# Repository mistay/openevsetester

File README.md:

# Welcome to OpenEVSEtester!

Based on EVSim's documentation (available at https://evsim.gonium.net/) this project tries to automate some basic tests required by [SAE J1772](https://de.wikipedia.org/wiki/SAE_J1772).

By now, this project features a PCB. An upcoming BOM, a Firmware (ESP-IDF) and a mobile app will be relased soon.

# Features
- Wallbox connector 7 PIN: L1, L2, L3, N, PE, CP, PP
- Microcontroller ESP32 (ESP32-S2-WROOM), in-circuit programmable by USB (USB-C) connector or serial (you'll need a $1 programmer, i.e. USB/Serial converter)
- both CP and PP protection by fuses and varistors
- battery (LIpO/LiIo) charger with system load: charge while using this device
- buck/boost converter (3V3) to use any available voltage from battery pack (2,4V to 4,2V)
- UI: display (both i2c oled and/or spi tft) tbd: one of this will be removed in further versions
- UI: rotary encoder for modern menu-browsing
- PE breaker: PE can be disconnected by software to simulate a broken PE wire
- PP isolated proximity resistor selection: choose between 100R, 220R, 680R, 1k5 and 4k7 to or any combination (in parallel) to simulate resistors that are outside specification and to test if the wallbox in test handles the voltage drop according to SAE J1772.
- simulate SAE J1772 states A, B, C and E
- simulate diode-fault by shortening diode
- isolated CP measurment by 10-bit 10ksamples/s adc
- isolated mains (L1, L2, L3) measurement by tranformers and internal ADC of ESP32 (voltage, frequency, phasing)
- cr2032 battery-backuped real time clock to timestamp measurements for reports w/o beeing online

```mermaid
graph LR

A[State A] --> B((read CP: 12V?))

B -- yes --> C[State B]
B -- no --> D(report error)
D --> A
C --> E((CP, PWM?))
E -- no --> G((report error))
G --> A
E -- yes --> F[State C]
F --> H((...))
```

# Firmware

A ESP-IDF based firmware for this device can be found here: https://github.com/mistay/openevsetester_firmware/

# mobile app (html/javascript based web if) (TBD!)
## Requirements
- manual mode (handle and read actuators and sensors)
- trigger automatic testinsg
- report downloading

## Credits
Special thanks for ideas, bugfixes and reviews,  [Philipp Aigner](https://aignerelektronik.at)

## License
MIT

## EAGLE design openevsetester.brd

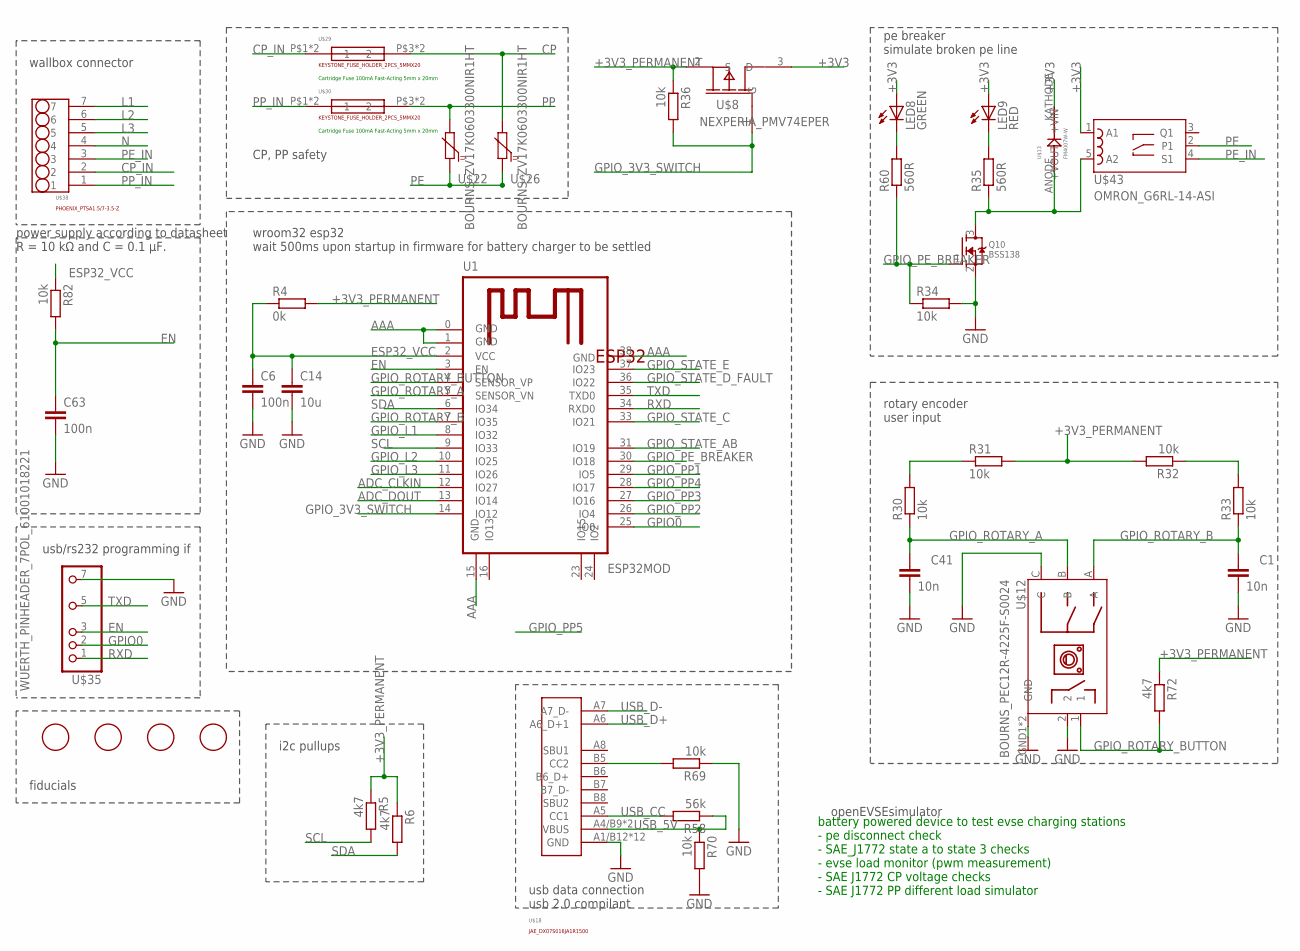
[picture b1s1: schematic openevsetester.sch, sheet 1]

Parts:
C1, C41: 10n; C0402
C6, C63: 100n; C0402
C14: 10u; C0805
LED8: GREEN; SML0603
LED9: RED; SML0603
Q10: BSS138; SOT23
R4: 0k; R0402
R5, R6, R72: 4k7; R0402
R30, R31, R32, R33, R34, R36, R69, R70, R82: 10k; R0402
R35, R60: 560R; R0402
R58: 56k; R0402
U1: ESP32MOD
U$8: NEXPERIA_PMV74EPER; SOT23
U$12: BOURNS_PEC12R-4225F-S0024; BOURNS_PEC12RXXX
U$13: FM4007W-W; SMX
U$18: JAE_DX07S016JA1R1500
U$19, U$21, U$23, U$24: FIDUCIAL; FIDUCIAL_1MM
U$22, U$26: BOURNS_ZV17K0603300NIR1HT; 0603
U$29, U$30: KEYSTONE_FUSE_HOLDER_2PCS_5MMX20; KEYSTONE_PC_5MM_FUSE_CLIP
U$35: WUERTH_PINHEADER_7POL_61001018221; PINHEADER_SMD_7POL_ESP32_PRG
U$38: PHOENIX_PTSA1.5/7-3.5-Z; PHOENIX_PTSA_7POL_3.5MM
U$43: OMRON_G6RL-14-ASI

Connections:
+3V3: LED8.A, LED9.A, U$8.3 (D), U$13.KATHODE (+VOUT), U$43.1 (A1); also elsewhere on the board
+3V3_PERMANENT: R4.2, R5.1, R6.1, R31.2, R32.2, R36.1, R72.1, U$8.2 (S); also elsewhere on the board
AAA: C1.2, C6.2, C14.2, C41.2, C63.2, Q10.2 (S), R34.2, R69.1, R70.2, U1.0 (GND), U1.1 (GND), U1.15 (GND), U1.38 (GND), U$12.2, U$12.C, U$12.GND1 (GND), U$12.GND2 (GND), U$18.A1/B12 (GND), U$18.A12/B1 (GND), U$18.G1 (GND), U$18.G2 (GND), U$18.G3 (GND), U$18.G4 (GND), U$18.G5 (GND), U$18.G6 (GND), U$18.G7 (GND), U$18.G8 (GND), U$18.P1 (GND), U$18.P2 (GND), U$35.7; also elsewhere on the board
ADC_CLKIN: U1.12 (IO27); also elsewhere on the board
ADC_DOUT: U1.13 (IO14); also elsewhere on the board
CP: U$26.1, U$29.P$3 (2), U$29.PAD2 (2); also elsewhere on the board
CP_IN: U$29.P$1 (1), U$29.PAD1 (1), U$38.2
EN: C63.1, R82.2, U1.3 (EN), U$35.3
ESP32_VCC: C6.1, C14.1, R4.1, R82.1, U1.2 (VCC)
GPIO0: U1.25 (IO0), U$35.2
GPIO_3V3_SWITCH: R36.2, U1.14 (IO12), U$8.1 (G)
GPIO_L1: U1.8 (IO32); also elsewhere on the board
GPIO_L2: U1.10 (IO25); also elsewhere on the board
GPIO_L3: U1.11 (IO26); also elsewhere on the board
GPIO_PE_BREAKER: Q10.1 (G), R34.1, R60.1, U1.30 (IO18)
GPIO_PP1: U1.29 (IO5); also elsewhere on the board
GPIO_PP2: U1.26 (IO4); also elsewhere on the board
GPIO_PP3: U1.27 (IO16); also elsewhere on the board
GPIO_PP4: U1.28 (IO17); also elsewhere on the board
GPIO_ROTARY_A: C41.1, R30.1, U1.5 (SENSOR_VN), U$12.B
GPIO_ROTARY_B: C1.1, R33.1, U1.7 (IO35), U$12.A
GPIO_ROTARY_BUTTON: R72.2, U1.4 (SENSOR_VP), U$12.1
GPIO_STATE_AB: U1.31 (IO19); also elsewhere on the board
GPIO_STATE_C: U1.33 (IO21); also elsewhere on the board
GPIO_STATE_D_FAULT: U1.36 (IO22); also elsewhere on the board
GPIO_STATE_E: U1.37 (IO23); also elsewhere on the board
L1: U$38.7; also elsewhere on the board
L2: U$38.6; also elsewhere on the board
L3: U$38.5; also elsewhere on the board
N: U$38.4; also elsewhere on the board
unnamed: LED9.C, R35.2
unnamed: Q10.3 (D), R35.1, U$13.ANODE (+VIN), U$43.5 (A2)
unnamed: LED8.C, R60.2
unnamed: R69.2, U$18.B5 (CC2)
unnamed: R30.2, R31.1
unnamed: R32.1, R33.2
PE: U$22.2, U$26.2, U$43.2 (P1); also elsewhere on the board
PE_IN: U$38.3, U$43.4 (S1)
PP: U$22.1, U$30.P$3 (2), U$30.PAD2 (2); also elsewhere on the board
PP_IN: U$30.P$1 (1), U$30.PAD1 (1), U$38.1
RXD: U1.34 (RXD0), U$35.1
SCL: R5.2, U1.9 (IO33); also elsewhere on the board
SDA: R6.2, U1.6 (IO34); also elsewhere on the board
TXD: U1.35 (TXD0), U$35.5
USB_5V: R58.1, R70.1, U$18.A4/B9 (VBUS), U$18.B4/A9 (VBUS)
USB_CC: R58.2, U$18.A5 (CC1)
USB_D+: U$18.A6 (A6_D+1)
USB_D-: U$18.A7 (A7_D-)

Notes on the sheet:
wallbox connector
openEVSEsimulator
battery powered device to test evse charging stations - pe disconnect check - SAE_J1772 state a to state 3 checks - evse load monitor (pwm measurement) - SAE J1772 CP voltage checks - SAE J1772 PP different load simulator
usb/rs232 programming if
fiducials
power supply according to datasheet R = 10 kΩ and C = 0.1 μF.
i2c pullups
wroom32 esp32 wait 500ms upon startup in firmware for battery charger to be settled
rotary encoder user input
CP, PP safety
Cartridge Fuse 100mA Fast-Acting 5mm x 20mm
pe breaker simulate broken pe line
usb data connection usb 2.0 compilant

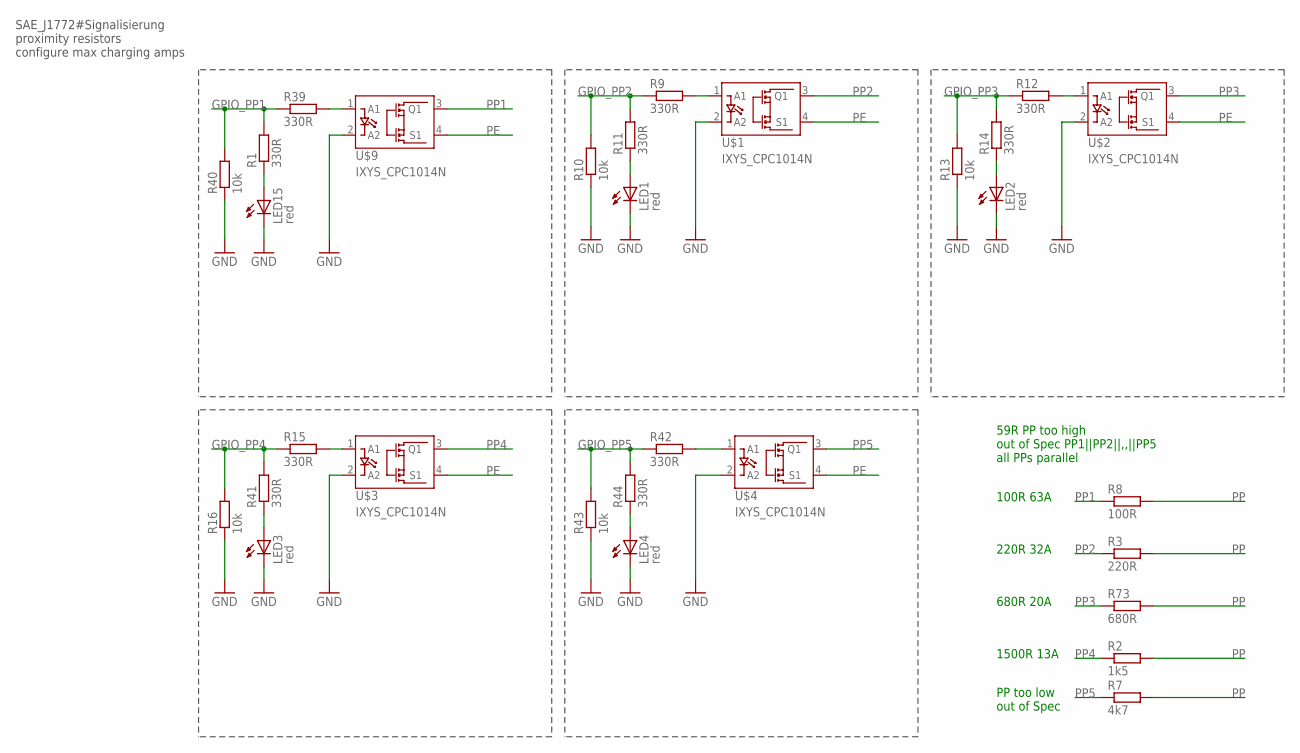
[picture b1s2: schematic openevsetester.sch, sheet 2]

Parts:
LED1, LED2, LED3, LED4, LED15: red; SML0603
R1, R9, R11, R12, R14, R15, R39, R41, R42, R44: 330R; R0402
R2: 1k5; R1210
R3: 220R; R1210
R7: 4k7; R1210
R8: 100R; R1210
R10, R13, R16, R40, R43: 10k; R0402
R73: 680R; R1210
U$1, U$2, U$3, U$4, U$9: IXYS_CPC1014N; SOIC-4

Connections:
AAA: LED1.C, LED2.C, LED3.C, LED4.C, LED15.C, R10.1, R13.1, R16.1, R40.1, R43.1, U$1.2 (A2), U$2.2 (A2), U$3.2 (A2), U$4.2 (A2), U$9.2 (A2); also elsewhere on the board
GPIO_PP1: R1.2, R39.1, R40.2; also elsewhere on the board
GPIO_PP2: R9.1, R10.2, R11.2; also elsewhere on the board
GPIO_PP3: R12.1, R13.2, R14.2; also elsewhere on the board
GPIO_PP4: R15.1, R16.2, R41.2; also elsewhere on the board
GPIO_PP5: R42.1, R43.2, R44.2
unnamed: R9.2, U$1.1 (A1)
unnamed: LED1.A, R11.1
unnamed: R12.2, U$2.1 (A1)
unnamed: LED2.A, R14.1
unnamed: R15.2, U$3.1 (A1)
unnamed: LED3.A, R41.1
unnamed: R42.2, U$4.1 (A1)
unnamed: R39.2, U$9.1 (A1)
unnamed: LED15.A, R1.1
unnamed: LED4.A, R44.1
PE: U$1.4 (S1), U$2.4 (S1), U$3.4 (S1), U$4.4 (S1), U$9.4 (S1); also elsewhere on the board
PP: R2.2, R3.2, R7.2, R8.2, R73.2; also elsewhere on the board
PP1: R8.1, U$9.3 (Q1)
PP2: R3.1, U$1.3 (Q1)
PP3: R73.1, U$2.3 (Q1)
PP4: R2.1, U$3.3 (Q1)
PP5: R7.1, U$4.3 (Q1)

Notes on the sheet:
SAE_J1772#Signalisierung proximity resistors configure max charging amps
100R 63A
220R 32A
680R 20A
1500R 13A
PP too low out of Spec
59R PP too high out of Spec PP1||PP2||,,||PP5 all PPs parallel

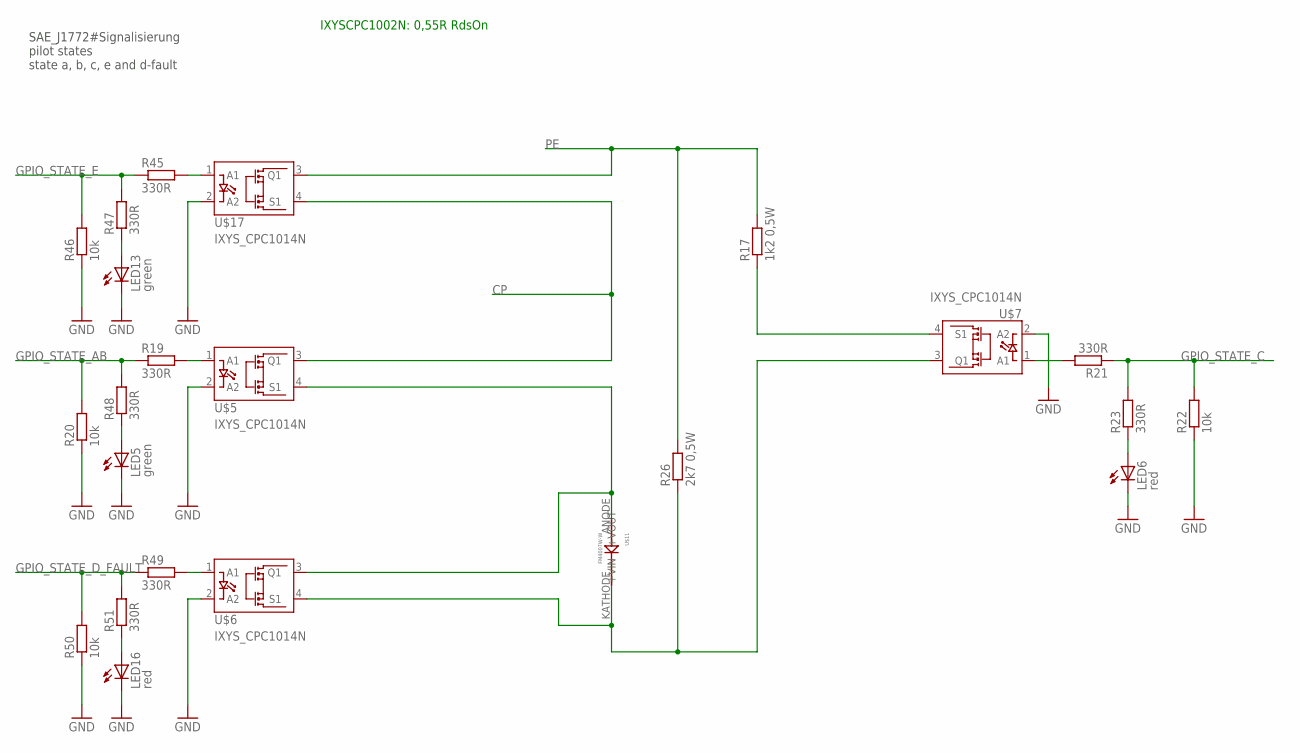
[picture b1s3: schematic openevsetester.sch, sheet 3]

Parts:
LED5, LED13: green; SML0603
LED6, LED16: red; SML0603
R17: 1k2 0,5W; R0805
R19, R21, R23, R45, R47, R48, R49, R51: 330R; R0402
R20, R22, R46, R50: 10k; R0402
R26: 2k7 0,5W; R0805
U$5, U$6, U$7, U$17: IXYS_CPC1014N; SOIC-4
U$11: FM4007W-W; SMX

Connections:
AAA: LED5.C, LED6.C, LED13.C, LED16.C, R20.1, R22.1, R46.1, R50.1, U$5.2 (A2), U$6.2 (A2), U$7.2 (A2), U$17.2 (A2); also elsewhere on the board
CP: U$5.3 (Q1), U$17.4 (S1); also elsewhere on the board
GPIO_STATE_AB: R19.1, R20.2, R48.2; also elsewhere on the board
GPIO_STATE_C: R21.1, R22.2, R23.2; also elsewhere on the board
GPIO_STATE_D_FAULT: R49.1, R50.2, R51.2; also elsewhere on the board
GPIO_STATE_E: R45.1, R46.2, R47.2; also elsewhere on the board
unnamed: R45.2, U$17.1 (A1)
unnamed: R19.2, U$5.1 (A1)
unnamed: R21.2, U$7.1 (A1)
unnamed: LED6.A, R23.1
unnamed: LED5.A, R48.1
unnamed: U$5.4 (S1), U$6.3 (Q1), U$11.ANODE (+VIN)
unnamed: LED13.A, R47.1
unnamed: R49.2, U$6.1 (A1)
unnamed: LED16.A, R51.1
PE: R17.2, R26.2, U$17.3 (Q1); also elsewhere on the board
PP6: R17.1, U$7.4 (S1)
PP7: R26.1, U$6.4 (S1), U$7.3 (Q1), U$11.KATHODE (+VOUT)

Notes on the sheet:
SAE_J1772#Signalisierung pilot states state a, b, c, e and d-fault
IXYSCPC1002N: 0,55R RdsOn

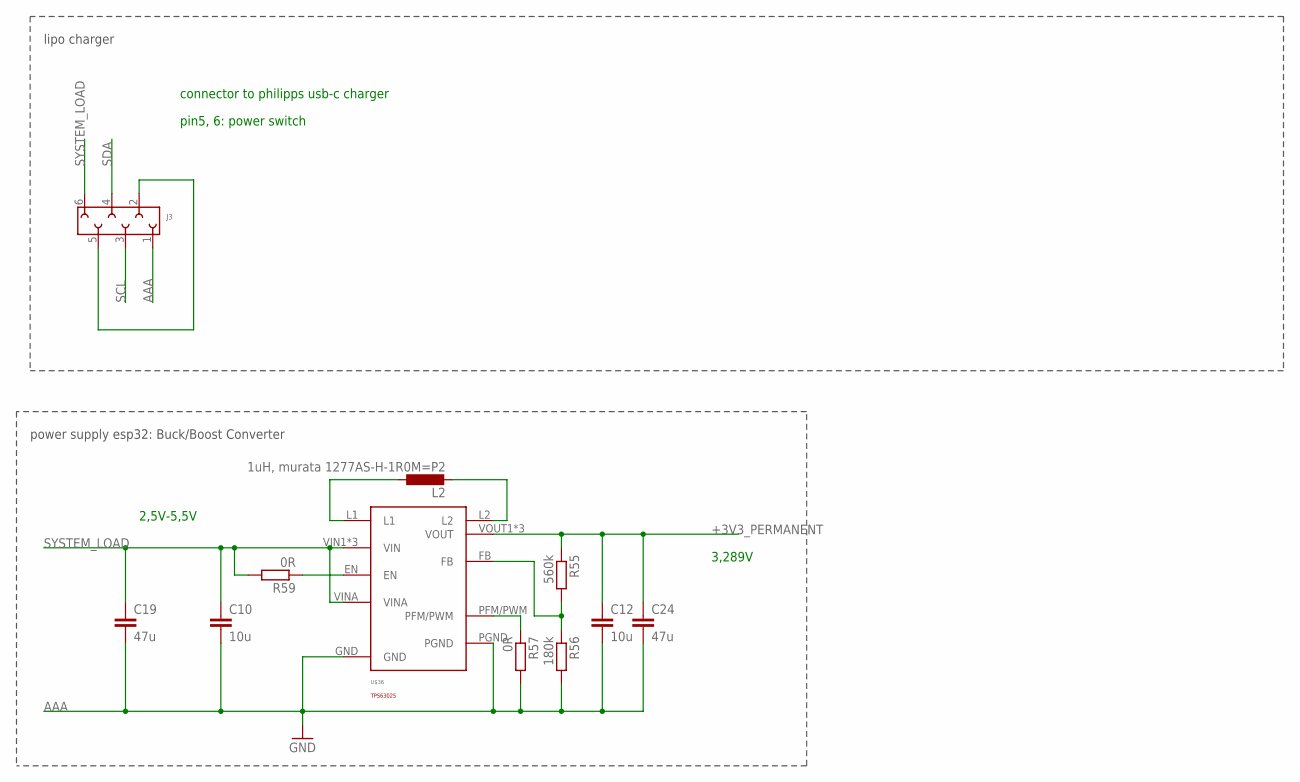
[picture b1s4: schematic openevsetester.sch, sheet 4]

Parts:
C10, C12: 10u; C0805
C19: 47u; C1206
C24: 47u; C0805
J3: 6100XX11921_61000611921; 61000611921
L2: 1uH, murata 1277AS-H-1R0M=P2; L3225M
R55: 560k; R0402
R56: 180k; R0402
R57, R59: 0R; R0402
U$36: TPS63025; VQFN14

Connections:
+3V3_PERMANENT: C12.1, C24.1, R55.1, U$36.VOUT1 (VOUT), U$36.VOUT2 (VOUT), U$36.VOUT3 (VOUT); also elsewhere on the board
AAA: C10.2, C12.2, C19.2, C24.2, J3.1, R56.2, R57.2, U$36.GND, U$36.PGND; also elsewhere on the board
L13V3: L2.1, U$36.L1
L23V3: L2.2, U$36.L2
unnamed: J3.2, J3.5
unnamed: R59.1, U$36.EN
unnamed: R55.2, R56.1, U$36.FB
unnamed: R57.1, U$36.PFM/PWM
SCL: J3.3; also elsewhere on the board
SDA: J3.4; also elsewhere on the board
SYSTEM_LOAD: C10.1, C19.1, J3.6, R59.2, U$36.VIN1 (VIN), U$36.VIN2 (VIN), U$36.VIN3 (VIN), U$36.VINA

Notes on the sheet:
lipo charger
power supply esp32: Buck/Boost Converter
2,5V-5,5V
3,289V
connector to philipps usb-c charger
pin5, 6: power switch

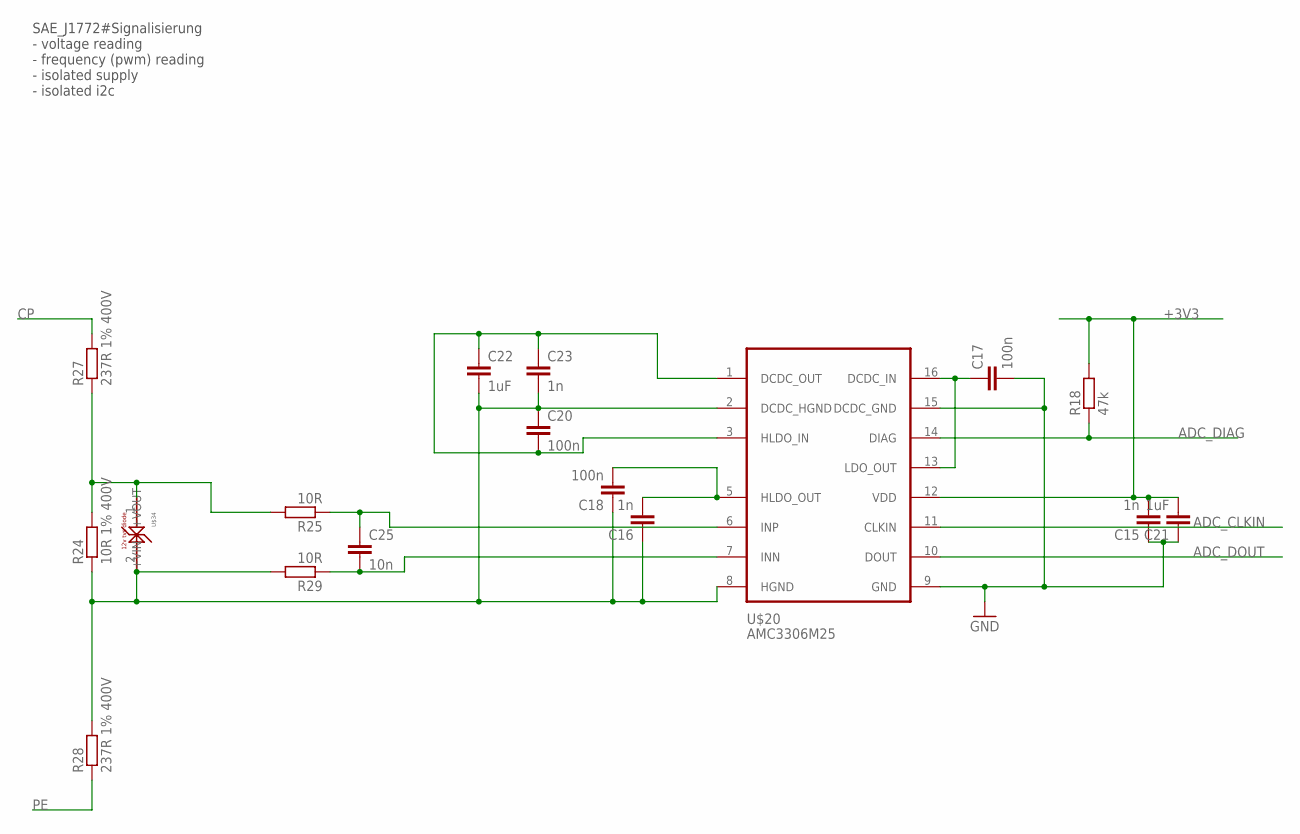
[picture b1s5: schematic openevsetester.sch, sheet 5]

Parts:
C15, C16: 1n; C1206
C17, C20: 100n; C0603
C18: 100n; C1206
C21: 1uF; C1206
C22: 1uF; C0603
C23: 1n; C0603
C25: 10n; C0603
R18: 47k; R0402
R24: 10R 1% 400V; R2512
R25, R29: 10R; R2512
R27, R28: 237R 1% 400V; R2010
U$20: AMC3306M25; SOIC-16
U$34: 12v tvs diode; 0402

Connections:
+3V3: C15.2, C21.2, R18.2, U$20.12 (VDD); also elsewhere on the board
AAA: C15.1, C17.2, C21.1, U$20.9 (GND), U$20.15 (DCDC_GND); also elsewhere on the board
ADC_CLKIN: U$20.11 (CLKIN); also elsewhere on the board
ADC_DIAG: R18.1, U$20.14 (DIAG)
ADC_DOUT: U$20.10 (DOUT); also elsewhere on the board
CP: R27.2; also elsewhere on the board
unnamed: C17.1, U$20.13 (LDO_OUT), U$20.16 (DCDC_IN)
unnamed: C25.1, R25.1, U$20.6 (INP)
unnamed: R24.2, R25.2, R27.1, U$34.1 (+VIN)
unnamed: C25.2, R29.1, U$20.7 (INN)
unnamed: C16.1, C18.1, C20.1, C22.2, C23.2, R24.1, R28.2, R29.2, U$20.2 (DCDC_HGND), U$20.8 (HGND), U$34.2 (+VOUT)
unnamed: C16.2, C18.2, U$20.5 (HLDO_OUT)
unnamed: C20.2, C22.1, C23.1, U$20.1 (DCDC_OUT), U$20.3 (HLDO_IN)
PE: R28.1; also elsewhere on the board

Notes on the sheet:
SAE_J1772#Signalisierung - voltage reading - frequency (pwm) reading - isolated supply - isolated i2c

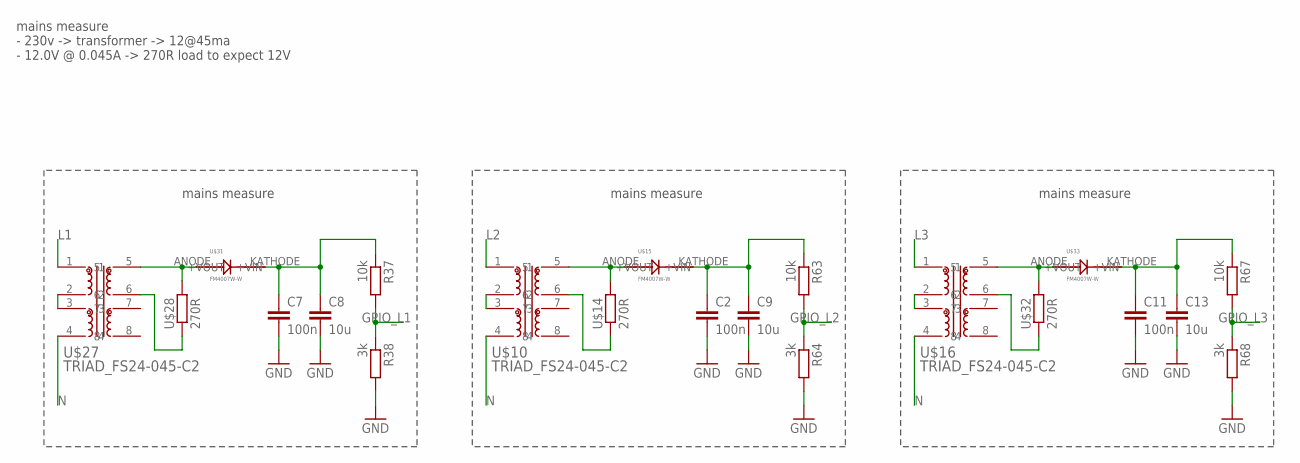
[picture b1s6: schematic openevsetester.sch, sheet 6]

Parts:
C2, C7, C11: 100n; C0402
C8, C9, C13: 10u; C0805
R37, R63, R67: 10k; R0402
R38, R64, R68: 3k; R0402
U$10, U$16, U$27: TRIAD_FS24-045-C2
U$14, U$28, U$32: 270R; 2512
U$15, U$31, U$33: FM4007W-W; SMX

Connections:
+3V2: C2.1, C9.1, R63.1, U$15.KATHODE (+VOUT)
+3V4: C11.1, C13.1, R67.1, U$33.KATHODE (+VOUT)
AAA: C2.2, C7.2, C8.2, C9.2, C11.2, C13.2, R38.2, R64.2, R68.2; also elsewhere on the board
GPIO_L1: R37.2, R38.1; also elsewhere on the board
GPIO_L2: R63.2, R64.1; also elsewhere on the board
GPIO_L3: R67.2, R68.1; also elsewhere on the board
L1: U$27.1; also elsewhere on the board
L2: U$10.1; also elsewhere on the board
L3: U$16.1; also elsewhere on the board
N: U$10.4, U$16.4, U$27.4; also elsewhere on the board
unnamed: U$10.2, U$10.3
unnamed: U$10.5, U$14.2, U$15.ANODE (+VIN)
unnamed: U$10.6, U$14.1
unnamed: U$16.2, U$16.3
unnamed: U$16.5, U$32.2, U$33.ANODE (+VIN)
unnamed: U$16.6, U$32.1
unnamed: C7.1, C8.1, R37.1, U$31.KATHODE (+VOUT)
unnamed: U$27.2, U$27.3
unnamed: U$27.5, U$28.2, U$31.ANODE (+VIN)
unnamed: U$27.6, U$28.1

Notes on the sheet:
mains measure - 230v -> transformer -> 12@45ma - 12.0V @ 0.045A -> 270R load to expect 12V
mains measure

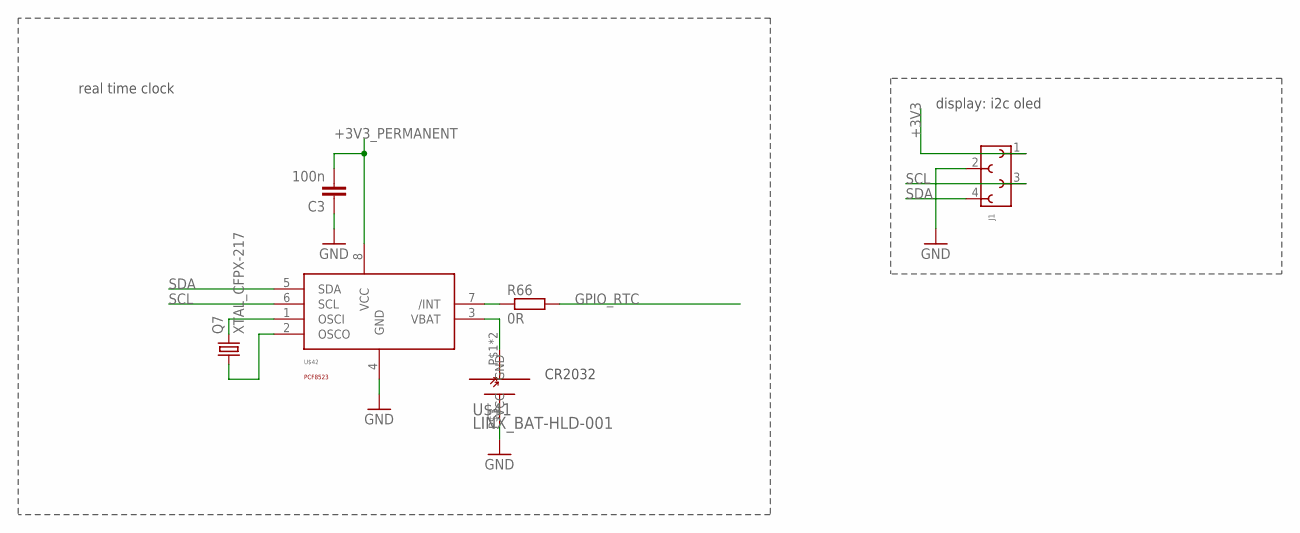
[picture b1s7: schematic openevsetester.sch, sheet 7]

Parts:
C3: 100n; C0402
J1: 6100XX11921_61000411921; 61000411921
Q7: XTAL_CFPX-217; FC-12M
R66: 0R; R0402
U$41: LINX_BAT-HLD-001; BATTERY_HOLDER_CR2032
U$42: PCF8523; SOIC-8

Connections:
+3V3: J1.1; also elsewhere on the board
+3V3_PERMANENT: C3.2, U$42.8 (VCC); also elsewhere on the board
AAA: C3.1, J1.2, U$41.P$3 (GND), U$42.4 (GND); also elsewhere on the board
GPIO_RTC: R66.2
unnamed: Q7.2, U$42.1 (OSCI)
unnamed: Q7.1, U$42.2 (OSCO)
unnamed: R66.1, U$42.7 (/INT)
SCL: J1.3, U$42.6 (SCL); also elsewhere on the board
SDA: J1.4, U$42.5 (SDA); also elsewhere on the board
VBAT: U$41.P$1 (VCC), U$41.P$2 (VCC), U$42.3 (VBAT)

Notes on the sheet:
real time clock
CR2032
display: i2c oled

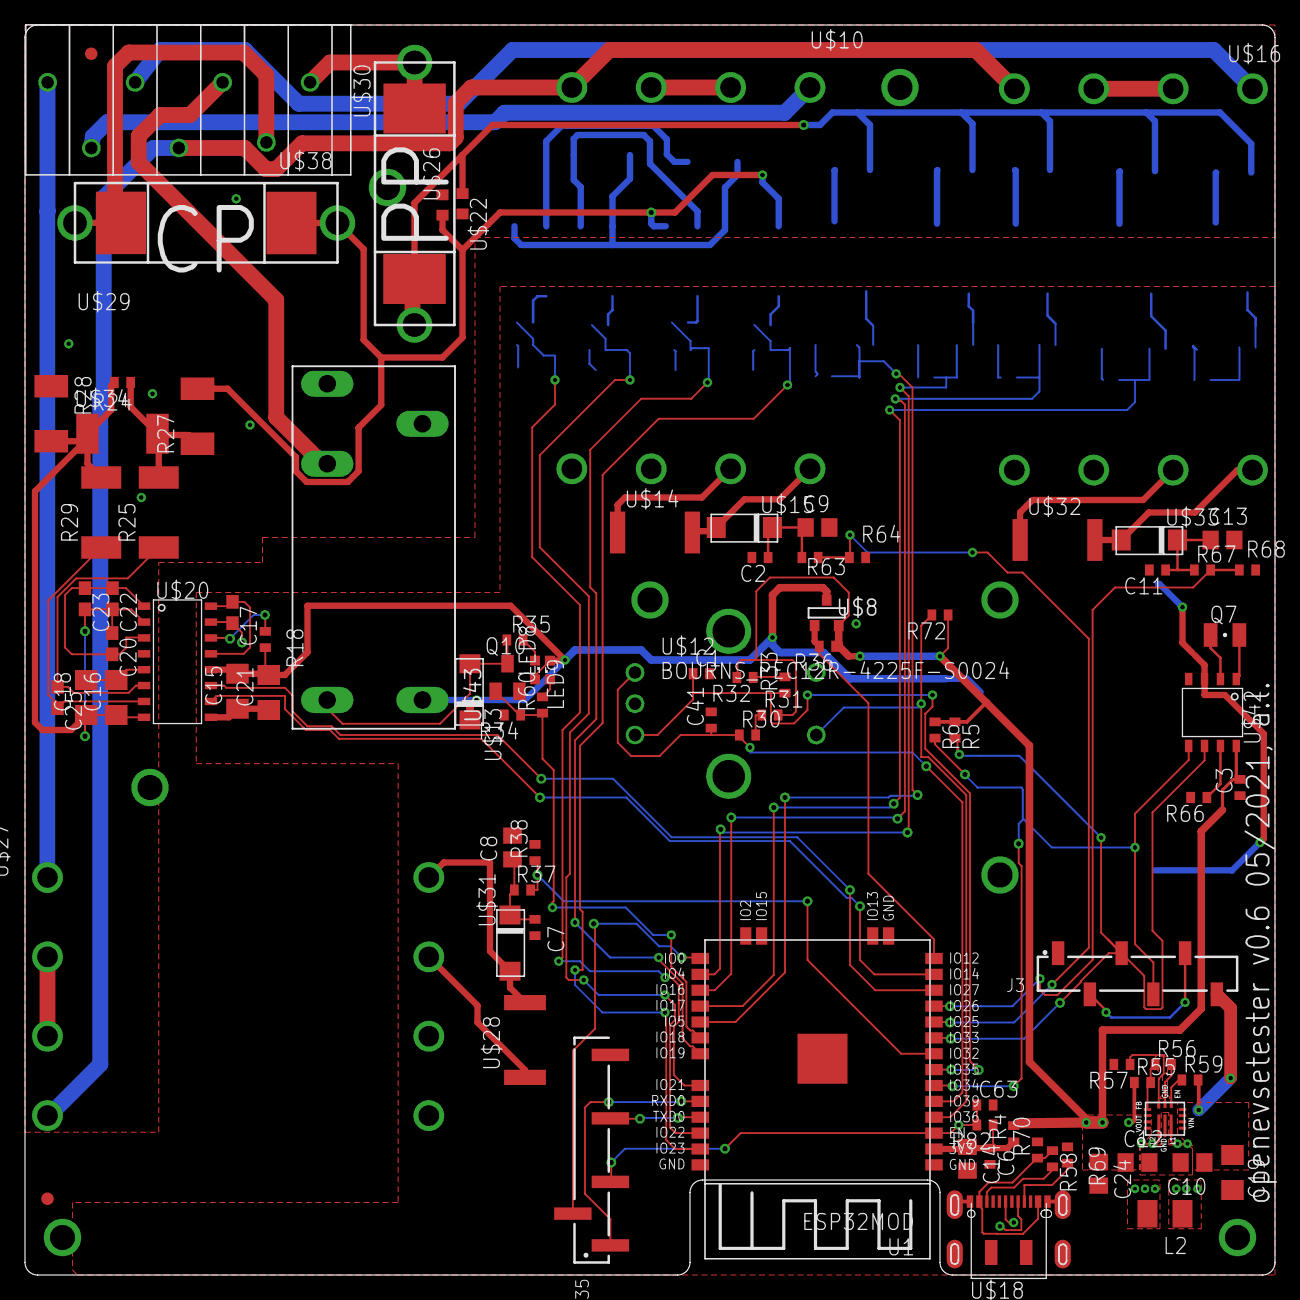
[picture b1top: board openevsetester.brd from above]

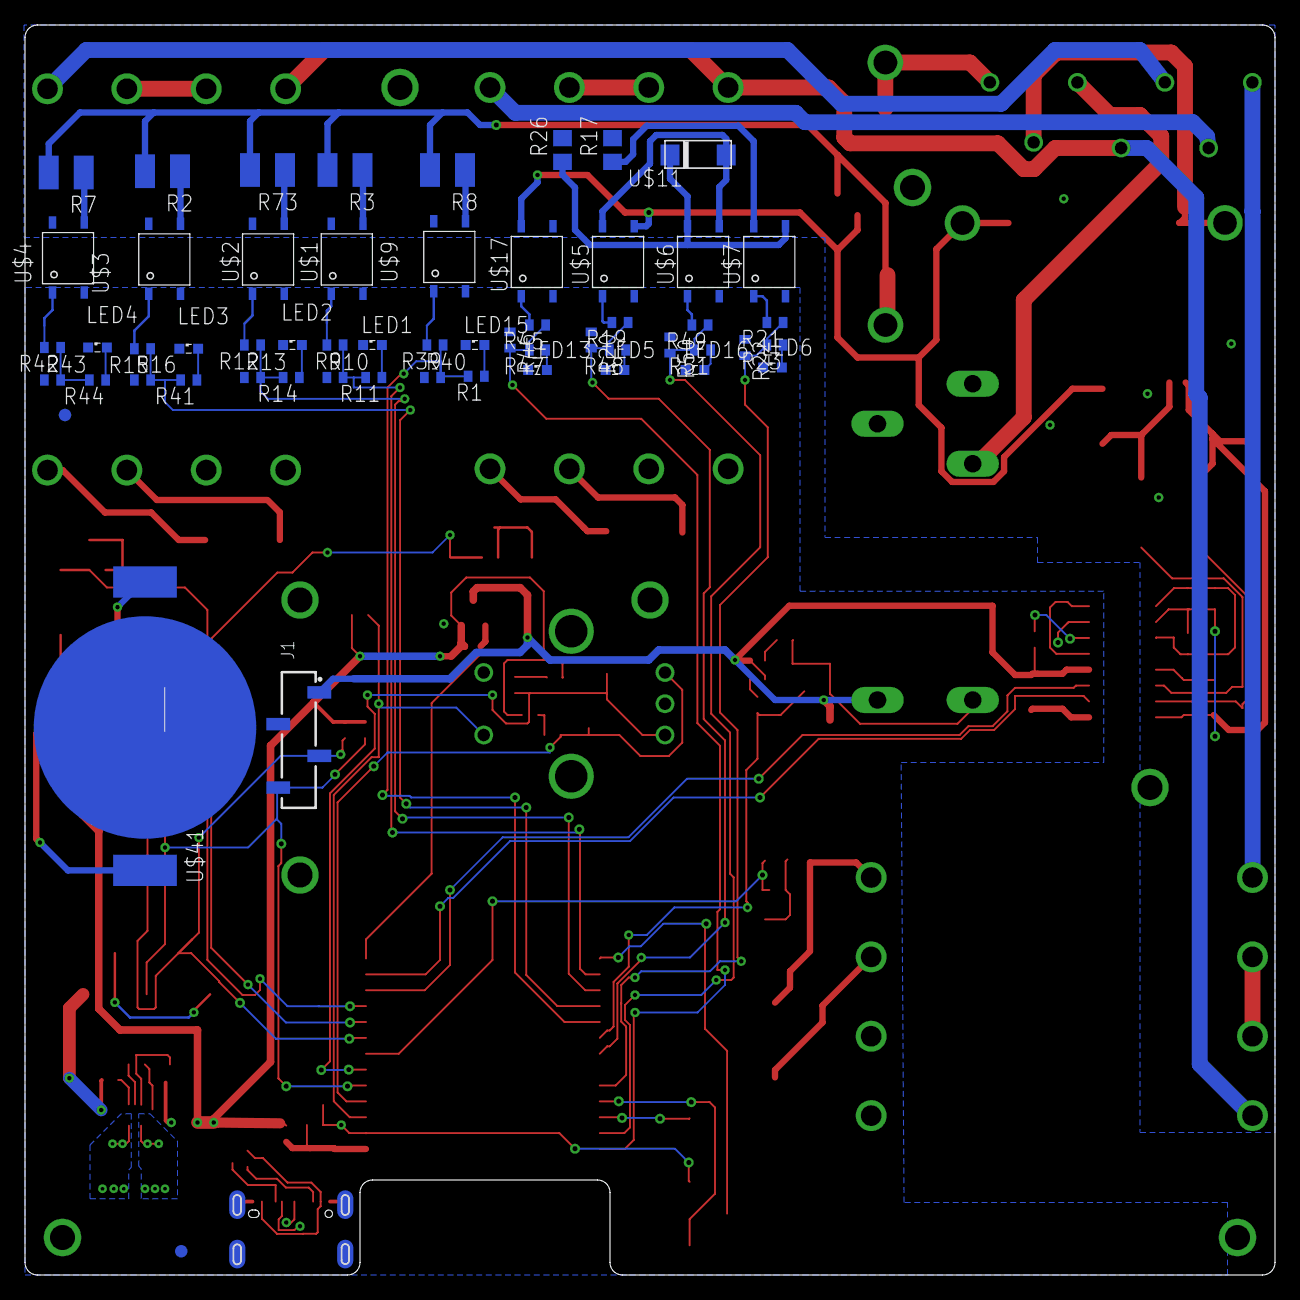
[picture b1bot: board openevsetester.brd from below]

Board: 2 copper layers, 100.0 x 100.0 mm, 148 parts (58 on the bottom side), 104 nets.

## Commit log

2021-01-11 init commit
2021-01-11 increased min hole size from 0.2 to 0.3 (to get cheaper offers), bumped to v0.5
2021-01-11 updated schematic pdf, removed old pdf, bumped to v0.5
2021-01-11 added partlist.txt
2021-01-11 added mouser basket, includes most (but not all) parts
2021-05-25 released v0.6 hardware
2021-05-25 isolated adc instead of dc/dc, op-amp and i2c isolator
2021-05-25 old-version cleanup
2021-05-25 renamed gerber zip files
2021-05-25 moved basket into bom_basked folder
2021-05-25 marked firmware folder as test folder
2021-05-25 updated partlist.txt to hw rev v0.6

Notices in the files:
parts and their libraries:
Wurth_Connectors_WR-PHD: Copyright: Würth Elektronik
